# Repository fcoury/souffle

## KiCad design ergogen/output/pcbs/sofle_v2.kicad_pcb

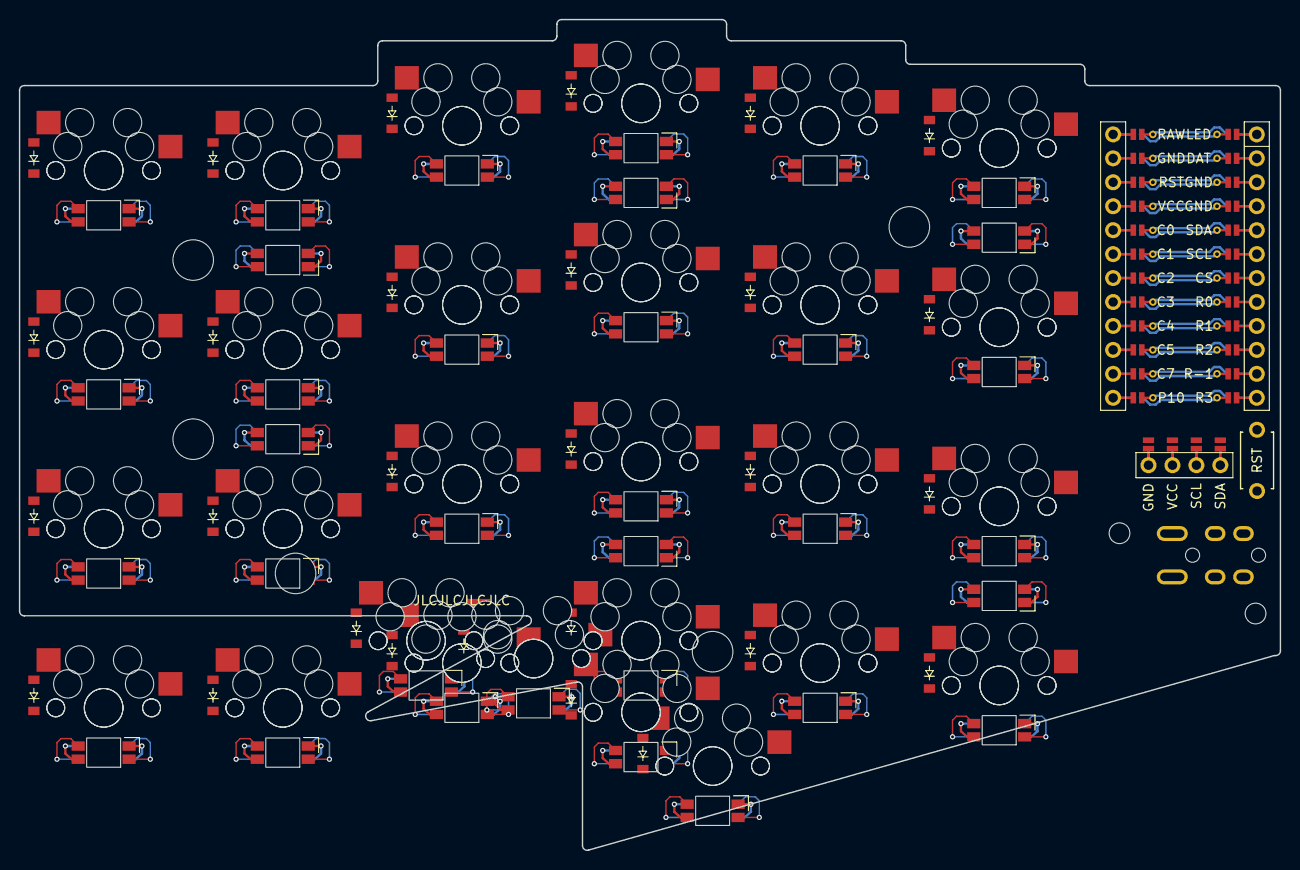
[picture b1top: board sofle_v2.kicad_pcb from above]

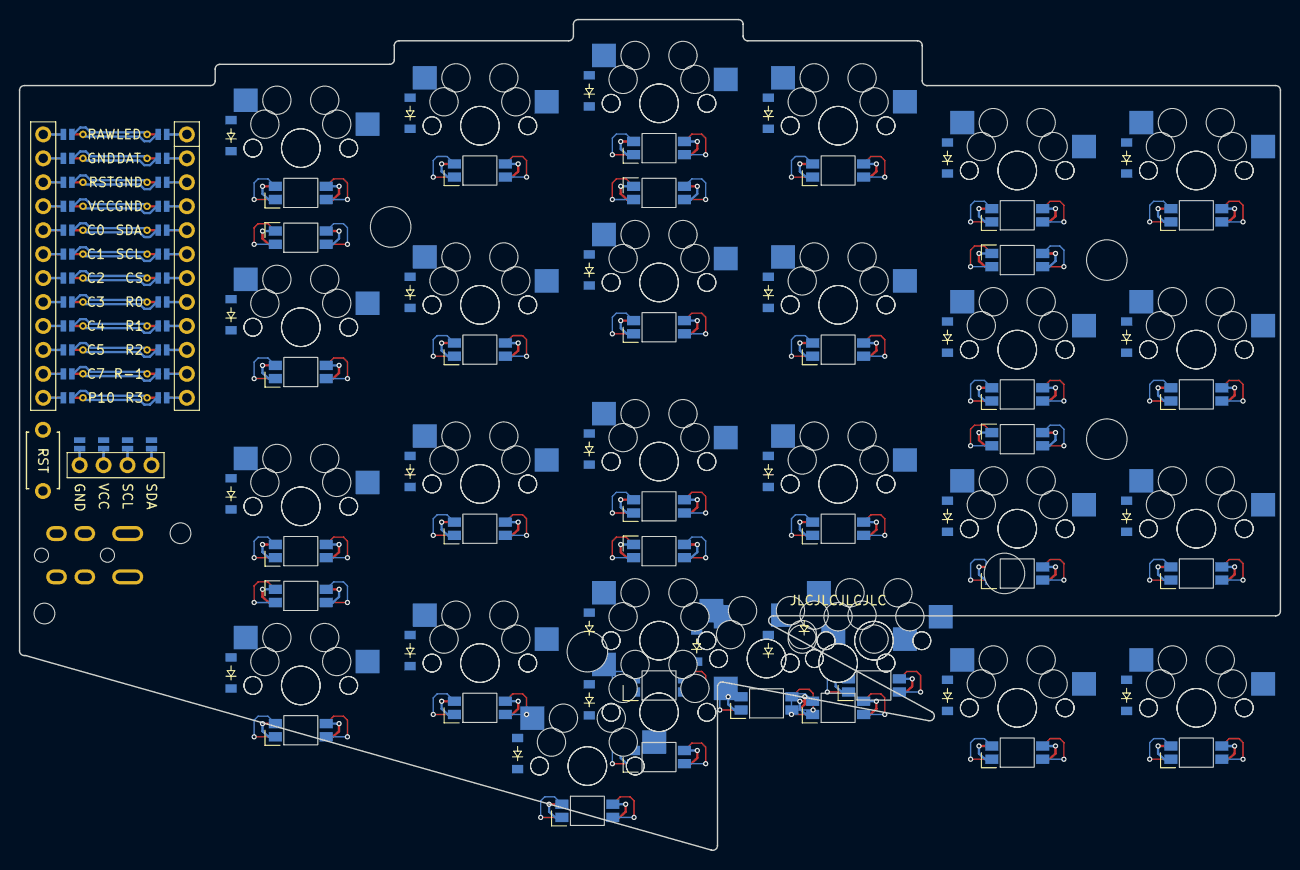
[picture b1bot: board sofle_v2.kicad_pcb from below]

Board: 2 copper layers, 133.8 x 88.1 mm, 157 parts (90 on the bottom side), 105 nets.

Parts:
D1, D2, D3, D4, D5, D6, D7, D8, D9, D10, D11, D12, D13, D14, D15, D16, D17, D18, D19, D20, D21, D22, D23, D24, D25, D26, D27, D28, D29, D30, D31, D32, D33, D34, D35, D36, D37, D38, D39, D40, D41, D42, D43, D44, D45, D46, D47, D48, D49, D50, D51, D52, D53, D54, D55, D56: diode_tht_sod123
DISP1: display_ssd1306
LED1, LED2, LED3, LED4, LED5, LED6, LED7, LED8, LED9, LED10, LED11, LED12, LED13, LED14, LED15, LED16, LED17, LED18, LED19, LED20, LED21, LED22, LED23, LED24, LED25, LED26, LED27, LED28: led_SK6812mini-e (per-key, reversible)
LED29, LED30, LED31, LED32, LED33, LED34: led_SK6812mini-e (underglow, reversible)
MCU1: mcu_nice_nano
MH1, MH2, MH3, MH4, MH5, MH6, MH7: mounting_hole_npth
RST1: reset_switch_tht_top
S1, S2, S3, S4, S5, S6, S7, S8, S9, S10, S11, S12, S13, S14, S15, S16, S17, S18, S19, S20, S21, S22, S23, S24, S25, S26, S27, S28, S29, S30, S31, S32, S33, S34, S35, S36, S37, S38, S39, S40, S41, S42, S43, S44, S45, S46, S47, S48, S49, S50, S51, S52, S53, S54, S55, S56: switch_mx
TRRS1: trrs_pj320a (reversible, symmetric)

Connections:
C0: MCU1.120, S1.1, S2.1, S3.1, S4.1, S29.1, S30.1, S31.1, S32.1
C1: MCU1.119, S5.1, S6.1, S7.1, S8.1, S33.1, S34.1, S35.1, S36.1
C2: MCU1.118, S9.1, S10.1, S11.1, S12.1, S37.1, S38.1, S39.1, S40.1
C3: MCU1.117, S13.1, S14.1, S15.1, S16.1, S41.1, S42.1, S43.1, S44.1
C4: MCU1.116, S17.1, S18.1, S19.1, S20.1, S45.1, S46.1, S47.1, S48.1
C5: MCU1.115, S21.1, S22.1, S23.1, S24.1, S49.1, S50.1, S51.1, S52.1
C6: S25.1, S53.1
C7: MCU1.114, S26.1, S54.1
C8: S27.1, S55.1
C9: S28.1, S56.1
DAT: MCU1.102, TRRS1.3
DISP1_1: DISP1.1, DISP1.13, DISP1.20
DISP1_2: DISP1.2, DISP1.12, DISP1.21
DISP1_3: DISP1.3, DISP1.11, DISP1.22
DISP1_4: DISP1.4, DISP1.10, DISP1.23
GND: DISP1.14, DISP1.24, LED1.3, LED2.3, LED3.3, LED4.3, LED5.3, LED6.3, LED7.3, LED8.3, LED9.3, LED10.3, LED11.3, LED12.3, LED13.3, LED14.3, LED15.3, LED16.3, LED17.3, LED18.3, LED19.3, LED20.3, LED21.3, LED22.3, LED23.3, LED24.3, LED25.3, LED26.3, LED27.3, LED28.3, LED29.3, LED30.3, LED31.3, LED32.3, LED33.3, LED34.3, MCU1.103, MCU1.104, MCU1.123, RST1.2, TRRS1.2
LED: LED29.4, MCU1.101
LED_2: LED22.2, LED23.4
LED_3: LED21.2, LED23.2, LED24.4
LED_4: LED17.2, LED20.4, LED21.4, LED24.2
LED_5: LED17.4, LED19.4, LED20.2
LED_6: LED18.4, LED19.2
LED_10: LED14.2, LED15.4
LED_11: LED13.2, LED15.2, LED16.4
LED_12: LED9.2, LED12.4, LED13.4, LED16.2
LED_13: LED9.4, LED11.4, LED12.2
LED_14: LED10.4, LED11.2
LED_15: LED6.4, LED10.2
LED_16: LED5.4, LED6.2, LED7.4
LED_17: LED5.2, LED7.2, LED8.4
LED_18: LED1.2, LED4.4, LED8.2
LED_19: LED1.4, LED3.4, LED4.2
LED_20: LED2.4, LED3.2
LED_21: LED2.2, LED25.4
LED_22: LED25.2, LED26.4
LED_23: LED26.2, LED27.4
LED_24: LED27.2, LED28.4
R0: D4.1, D8.1, D12.1, D16.1, D20.1, D24.1, D32.1, D36.1, D40.1, D44.1, D48.1, D52.1, MCU1.108
R1: D3.1, D7.1, D11.1, D15.1, D19.1, D23.1, D31.1, D35.1, D39.1, D43.1, D47.1, D51.1, MCU1.109
R2: D2.1, D6.1, D10.1, D14.1, D18.1, D22.1, D30.1, D34.1, D38.1, D42.1, D46.1, D50.1, MCU1.110
R3: D25.1, D26.1, D27.1, D28.1, D53.1, D54.1, D55.1, D56.1, MCU1.112
R-1: D1.1, D5.1, D9.1, D13.1, D17.1, D21.1, D29.1, D33.1, D37.1, D41.1, D45.1, D49.1, MCU1.111
RST: MCU1.122, RST1.1
SCL: DISP1.16, DISP1.26, MCU1.106
SDA: DISP1.17, DISP1.27, MCU1.105
ULED_1: LED29.2, LED30.4
ULED_2: LED30.2, LED31.4
ULED_3: LED31.2, LED32.4
ULED_4: LED32.2, LED33.4
ULED_5: LED33.2, LED34.4
VCC: DISP1.15, DISP1.25, LED1.1, LED2.1, LED3.1, LED4.1, LED5.1, LED6.1, LED7.1, LED8.1, LED9.1, LED10.1, LED11.1, LED12.1, LED13.1, LED14.1, LED15.1, LED16.1, LED17.1, LED18.1, LED19.1, LED20.1, LED21.1, LED22.1, LED23.1, LED24.1, LED25.1, LED26.1, LED27.1, LED28.1, LED29.1, LED30.1, LED31.1, LED32.1, LED33.1, LED34.1, MCU1.121, TRRS1.4
extra_outward_home_B: D28.2, S28.2
extra_outward_home_F: D56.2, S56.2
index_bottom_B: D18.2, S18.2
index_bottom_F: D46.2, S46.2
index_home_B: D19.2, S19.2
index_home_F: D47.2, S47.2
index_number_B: D17.2, S17.2
index_number_F: D45.2, S45.2
index_top_B: D20.2, S20.2
index_top_F: D48.2, S48.2
inner_bottom_B: D22.2, S22.2
inner_bottom_F: D50.2, S50.2
inner_home_B: D23.2, S23.2
inner_home_F: D51.2, S51.2
inner_number_B: D21.2, S21.2
inner_number_F: D49.2, S49.2
inner_top_B: D24.2, S24.2
inner_top_F: D52.2, S52.2
inward_home_B: D25.2, S25.2
inward_home_F: D53.2, S53.2
middle_bottom_B: D14.2, S14.2
middle_bottom_F: D42.2, S42.2
middle_home_B: D15.2, D26.2, S15.2, S26.2
middle_home_F: D43.2, D54.2, S43.2, S54.2
middle_number_B: D13.2, S13.2
middle_number_F: D41.2, S41.2
middle_top_B: D16.2, S16.2
middle_top_F: D44.2, S44.2
outer_bottom_B: D2.2, S2.2
outer_bottom_F: D30.2, S30.2
outer_home_B: D3.2, S3.2
outer_home_F: D31.2, S31.2
outer_number_B: D1.2, S1.2
outer_number_F: D29.2, S29.2
outer_top_B: D4.2, S4.2
outer_top_F: D32.2, S32.2
outward_home_B: D27.2, S27.2
outward_home_F: D55.2, S55.2
pinky_bottom_B: D6.2, S6.2
pinky_bottom_F: D34.2, S34.2
pinky_home_B: D7.2, S7.2
pinky_home_F: D35.2, S35.2
pinky_number_B: D5.2, S5.2
pinky_number_F: D33.2, S33.2
pinky_top_B: D8.2, S8.2
pinky_top_F: D36.2, S36.2
ring_bottom_B: D10.2, S10.2
ring_bottom_F: D38.2, S38.2
ring_home_B: D11.2, S11.2
ring_home_F: D39.2, S39.2
ring_number_B: D9.2, S9.2
ring_number_F: D37.2, S37.2
ring_top_B: D12.2, S12.2
ring_top_F: D40.2, S40.2

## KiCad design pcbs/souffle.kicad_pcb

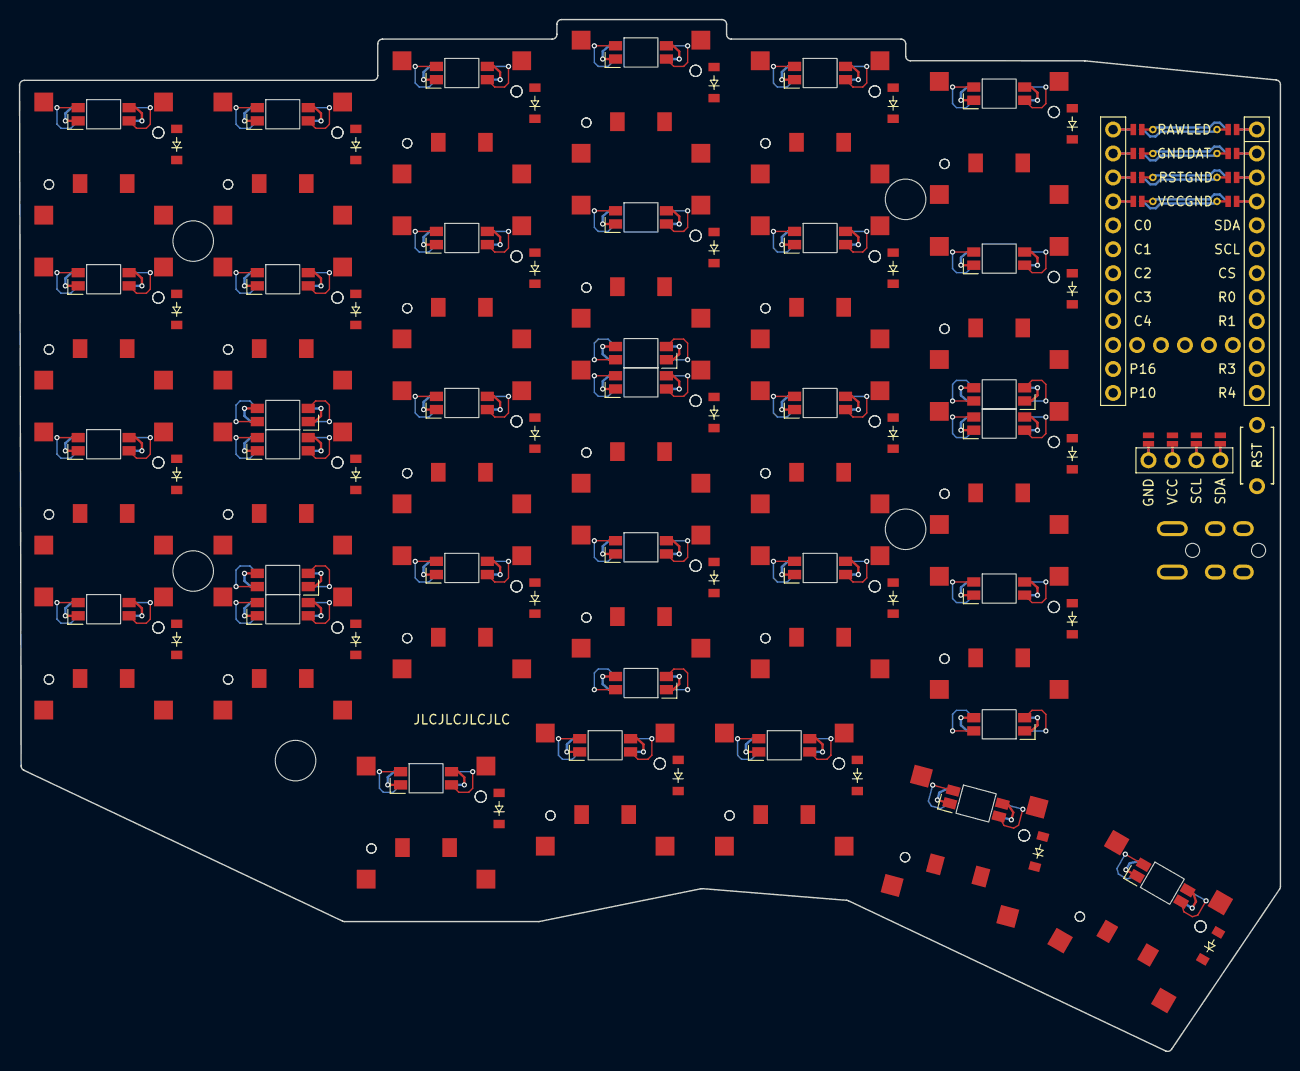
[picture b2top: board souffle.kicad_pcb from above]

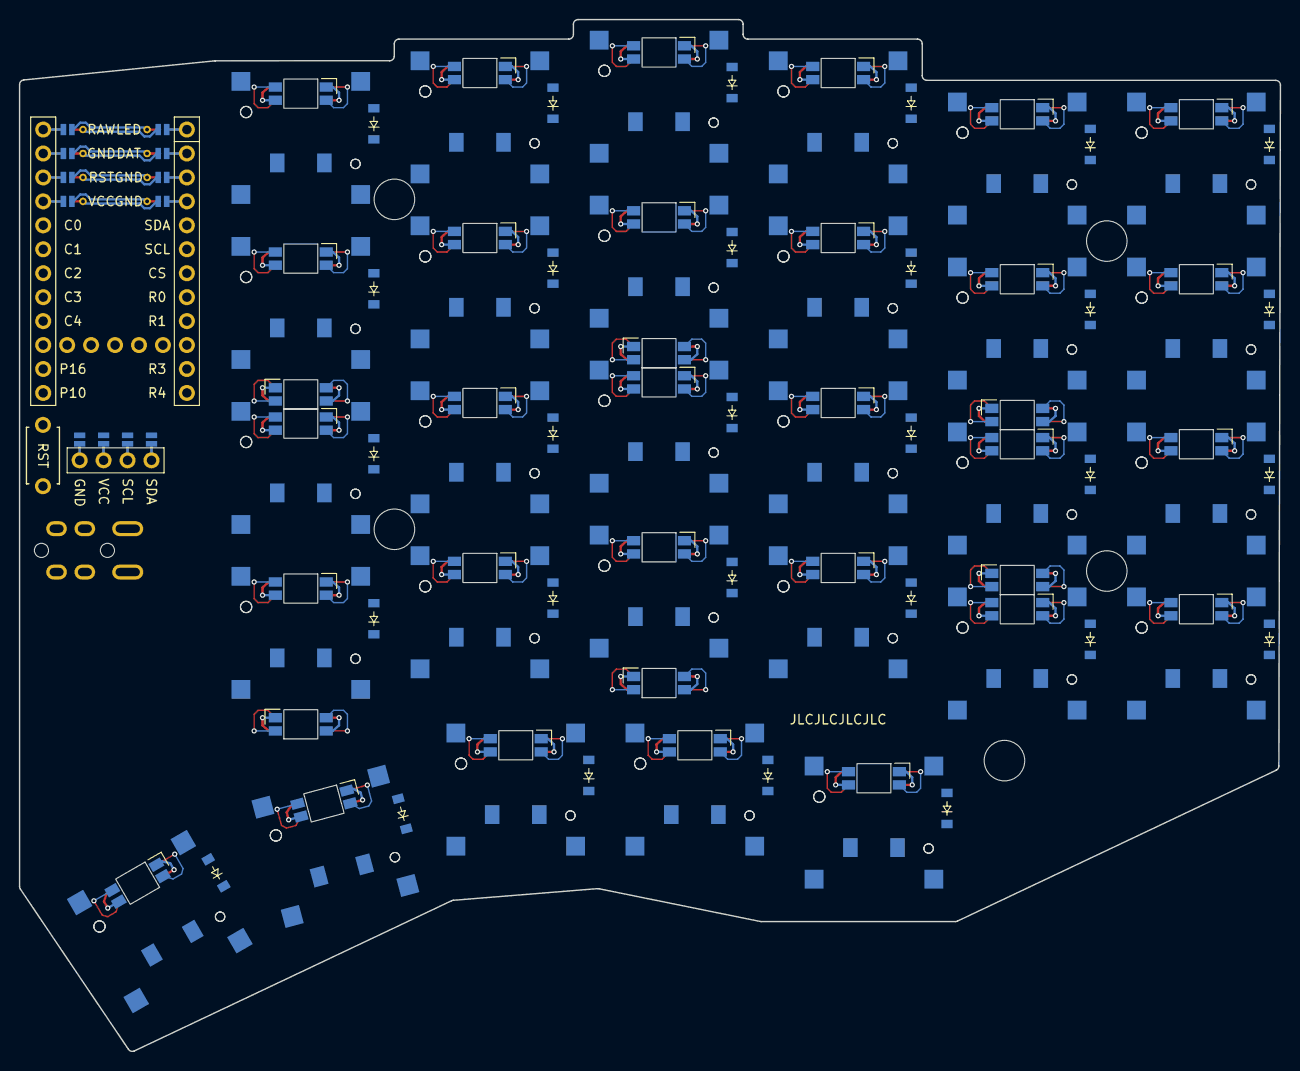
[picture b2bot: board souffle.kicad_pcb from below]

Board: 2 copper layers, 133.8 x 109.5 mm, 160 parts (93 on the bottom side), 113 nets.

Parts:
D1, D2, D3, D4, D5, D6, D7, D8, D9, D10, D11, D12, D13, D14, D15, D16, D17, D18, D19, D20, D21, D22, D23, D24, D25, D26, D27, D28, D29, D30, D31, D32, D33, D34, D35, D36, D37, D38, D39, D40, D41, D42, D43, D44, D45, D46, D47, D48, D49, D50, D51, D52, D53, D54, D55, D56, D57, D58: diode_tht_sod123
DISP1: display_ssd1306
LED1, LED2, LED3, LED4, LED5, LED6, LED7, LED8, LED9, LED10, LED11, LED12, LED13, LED14, LED15, LED16, LED17, LED18, LED19, LED20, LED21, LED22, LED23, LED24, LED25, LED26, LED27, LED28, LED29: led_SK6812mini-e (per-key, reversible)
LED30, LED31, LED32, LED33, LED34, LED35: led_SK6812mini-e (underglow, reversible)
MCU1: mcu_nice_nano
MH1, MH2, MH3, MH4, MH5: mounting_hole_npth
RST1: reset_switch_tht_top
S1, S2, S3, S4, S5, S6, S7, S8, S9, S10, S11, S12, S13, S14, S15, S16, S17, S18, S19, S20, S21, S22, S23, S24, S25, S26, S27, S28, S29, S30, S31, S32, S33, S34, S35, S36, S37, S38, S39, S40, S41, S42, S43, S44, S45, S46, S47, S48, S49, S50, S51, S52, S53, S54, S55, S56, S57, S58: CPG1316S01D02_mikeholscher
TRRS1: trrs_pj320a (reversible, symmetric)

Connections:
C0: MCU1.20, S1.2, S2.2, S3.2, S4.2, S30.2, S31.2, S32.2, S33.2
C1: MCU1.19, S5.2, S6.2, S7.2, S8.2, S25.2, S34.2, S35.2, S36.2, S37.2, S54.2
C2: MCU1.18, S9.2, S10.2, S11.2, S12.2, S26.2, S38.2, S39.2, S40.2, S41.2, S55.2
C3: MCU1.17, S13.2, S14.2, S15.2, S16.2, S27.2, S42.2, S43.2, S44.2, S45.2, S56.2
C4: MCU1.16, S17.2, S18.2, S19.2, S20.2, S28.2, S46.2, S47.2, S48.2, S49.2, S57.2
C5: MCU1.15, S21.2, S22.2, S23.2, S24.2, S29.2, S50.2, S51.2, S52.2, S53.2, S58.2
DAT: MCU1.102, TRRS1.3
DISP1_1: DISP1.1, DISP1.13, DISP1.20
DISP1_2: DISP1.2, DISP1.12, DISP1.21
DISP1_3: DISP1.3, DISP1.11, DISP1.22
DISP1_4: DISP1.4, DISP1.10, DISP1.23
GND: DISP1.14, DISP1.24, LED1.3, LED2.3, LED3.3, LED4.3, LED5.3, LED6.3, LED7.3, LED8.3, LED9.3, LED10.3, LED11.3, LED12.3, LED13.3, LED14.3, LED15.3, LED16.3, LED17.3, LED18.3, LED19.3, LED20.3, LED21.3, LED22.3, LED23.3, LED24.3, LED25.3, LED26.3, LED27.3, LED28.3, LED29.3, LED30.3, LED31.3, LED32.3, LED33.3, LED34.3, LED35.3, MCU1.103, MCU1.104, MCU1.123, RST1.2, TRRS1.2
LED: LED30.4, MCU1.101
LED_1: LED21.4, LED29.2
LED_2: LED21.2, LED22.4
LED_3: LED22.2, LED23.4
LED_4: LED23.2, LED24.4
LED_5: LED20.4, LED24.2
LED_6: LED19.4, LED20.2
LED_7: LED18.4, LED19.2
LED_15: LED27.4, LED28.2
LED_16: LED26.4, LED27.2
LED_17: LED25.4, LED26.2
LED_18: LED13.4, LED25.2
LED_19: LED13.2, LED14.4
LED_20: LED14.2, LED15.4
LED_21: LED15.2, LED16.4
LED_22: LED12.4, LED16.2
LED_23: LED11.4, LED12.2
LED_24: LED10.4, LED11.2
LED_25: LED9.4, LED10.2
LED_26: LED5.4, LED9.2
LED_27: LED5.2, LED6.4
LED_28: LED6.2, LED7.4
LED_29: LED7.2, LED8.4
LED_32: LED3.4, LED4.2
LED_33: LED2.4, LED3.2
LED_34: LED1.4, LED2.2
P101: MCU1.25, MCU1.28
P102: MCU1.26, MCU1.29
R0: D4.1, D8.1, D12.1, D16.1, D20.1, D24.1, D33.1, D37.1, D41.1, D45.1, D49.1, D53.1, MCU1.8
R1: D3.1, D7.1, D11.1, D15.1, D19.1, D23.1, D32.1, D36.1, D40.1, D44.1, D48.1, D52.1, MCU1.9
R2: D2.1, D6.1, D10.1, D14.1, D18.1, D22.1, D31.1, D35.1, D39.1, D43.1, D47.1, D51.1, MCU1.10
R3: D1.1, D5.1, D9.1, D13.1, D17.1, D21.1, D30.1, D34.1, D38.1, D42.1, D46.1, D50.1, MCU1.11
R4: D25.1, D26.1, D27.1, D28.1, D29.1, D54.1, D55.1, D56.1, D57.1, D58.1, MCU1.12
RST: MCU1.122, RST1.1
SCL: DISP1.16, DISP1.26, MCU1.6
SDA: DISP1.17, DISP1.27, MCU1.5
ULED_1: LED30.2, LED31.4
ULED_2: LED31.2, LED32.4
ULED_3: LED32.2, LED33.4
ULED_4: LED33.2, LED34.4
ULED_5: LED34.2, LED35.4
ULED_6: LED29.4, LED35.2
VCC: DISP1.15, DISP1.25, LED1.1, LED2.1, LED3.1, LED4.1, LED5.1, LED6.1, LED7.1, LED8.1, LED9.1, LED10.1, LED11.1, LED12.1, LED13.1, LED14.1, LED15.1, LED16.1, LED17.1, LED18.1, LED19.1, LED20.1, LED21.1, LED22.1, LED23.1, LED24.1, LED25.1, LED26.1, LED27.1, LED28.1, LED29.1, LED30.1, LED31.1, LED32.1, LED33.1, LED34.1, LED35.1, MCU1.121, TRRS1.4
big_outward_home_B: D29.2, S29.1
big_outward_home_F: D58.2, S58.1
extra_outward_home_B: D28.2, S28.1
extra_outward_home_F: D57.2, S57.1
index_bottom_B: D17.2, S17.1
index_bottom_F: D46.2, S46.1
index_home_B: D18.2, S18.1
index_home_F: D47.2, S47.1
index_number_B: D20.2, S20.1
index_number_F: D49.2, S49.1
index_top_B: D19.2, S19.1
index_top_F: D48.2, S48.1
inner_bottom_B: D21.2, S21.1
inner_bottom_F: D50.2, S50.1
inner_home_B: D22.2, S22.1
inner_home_F: D51.2, S51.1
inner_number_B: D24.2, S24.1
inner_number_F: D53.2, S53.1
inner_top_B: D23.2, S23.1
inner_top_F: D52.2, S52.1
inward_home_B: D25.2, S25.1
inward_home_F: D54.2, S54.1
mid_home_B: D26.2, S26.1
mid_home_F: D55.2, S55.1
middle_bottom_B: D13.2, S13.1
middle_bottom_F: D42.2, S42.1
middle_home_B: D14.2, S14.1
middle_home_F: D43.2, S43.1
middle_number_B: D16.2, S16.1
middle_number_F: D45.2, S45.1
middle_top_B: D15.2, S15.1
middle_top_F: D44.2, S44.1
outer_bottom_B: D1.2, S1.1
outer_bottom_F: D30.2, S30.1
outer_home_B: D2.2, S2.1
outer_home_F: D31.2, S31.1
outer_number_B: D4.2, S4.1
outer_number_F: D33.2, S33.1
outer_top_B: D3.2, S3.1
outer_top_F: D32.2, S32.1
outward_home_B: D27.2, S27.1
outward_home_F: D56.2, S56.1
pinky_bottom_B: D5.2, S5.1
pinky_bottom_F: D34.2, S34.1
pinky_home_B: D6.2, S6.1
pinky_home_F: D35.2, S35.1
pinky_number_B: D8.2, S8.1
pinky_number_F: D37.2, S37.1
pinky_top_B: D7.2, S7.1
pinky_top_F: D36.2, S36.1
ring_bottom_B: D9.2, S9.1
ring_bottom_F: D38.2, S38.1
ring_home_B: D10.2, S10.1
ring_home_F: D39.2, S39.1
ring_number_B: D12.2, S12.1
ring_number_F: D41.2, S41.1
ring_top_B: D11.2, S11.1
ring_top_F: D40.2, S40.1
